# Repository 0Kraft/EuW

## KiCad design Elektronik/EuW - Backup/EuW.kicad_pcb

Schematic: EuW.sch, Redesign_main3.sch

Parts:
C1, C4: 220; E2_5RE
C2, C3: 104; C025-024X044
D1: 14001; DO41-7.6
J3, J4: 1X2-3.5MM
P1, P2: CONN_02X05; Pin_Header_Angled_2x05_Pitch2.54mm
P4: CONN_01X03; Pin_Header_Straight_1x03_Pitch2.54mm
Q1, Q3, Q5: BC548; TO-92_Molded_Narrow
Q2, Q4: IRF4905; TO-220_Vertical
R1, R2, R3, R4, R11, R12: 10000; 0207_2V
R5, R6, R7, R8: 10MOhm; 0207_2V
R9: 470; 0207_2V
R10: 970; 0207_2V
U$1: NANO
U$2: RPI-ZERO; RASPBERRYPI_BASTELSTUBE_V13_RASPI_BOARD_B+_FULL
U$3, U$4: CP8-ADJ

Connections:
/5V0@1: C1.+, D1.C, Q4.3, R4.2, U$1.5V (5.5V)
/5VRPI: Q4.2, R12.1, U$2.2 (5V0)
/D2: P1.1, U$1.D2
/D3: P1.3, U$1.D3
/D4: P1.5, U$1.D4
/D5: P1.7, U$1.D5
/D6: P1.9, U$1.D6
/D7: P2.1, U$1.D7
/D8: P2.3, U$1.D8
/D9: P2.5, U$1.D9
/D10: P2.7, U$1.D10
/D11: P2.9, U$1.D11
/N$1: D1.A, U$4.OUT+
/N$3: J4.2, Q2.3, R2.2, R6.1
/N$11: J3.2, R8.1, U$4.IN+
/N$12: J3.1, U$4.IN-
/N$14: C3.2, R7.1, R8.2, U$1.A1
/N$15: R9.1, U$1.TX0
/N$16: Q5.1, R12.2, U$1.RX1
/N$17: Q5.3, U$2.8 (TXD0/GPIO14)
/N$18: R9.2, R10.1, U$2.10 (RXD0/GPIO15)
/N$20: C4.+, U$1.RST
GND: C1.-, C2.2, C3.1, J4.1, P1.6, P1.8, P1.10, P2.6, P2.8, P2.10, P4.1, Q1.3, Q3.3, R5.1, R7.2, R10.2, U$1.GND1 (GND2), U$2.9 (GND), U$3.IN-, U$3.OUT-, U$4.OUT-; also elsewhere on the board
unnamed: C2.1, R5.2, R6.2, U$1.A2
unnamed: C4.-, U$1.GND
unnamed: P1.2, P1.4, P2.2, P2.4, P4.2, U$3.OUT+
unnamed: P4.3, U$1.A0
unnamed: Q1.1, Q2.1, R2.1
unnamed: Q1.2, R1.1
unnamed: Q2.2, U$3.IN+
unnamed: Q3.1, Q4.1, R4.1
unnamed: Q3.2, R3.1
unnamed: Q5.2, R11.1
unnamed: R1.2, U$1.A6
unnamed: R3.2, U$1.A7
unnamed: R11.2, U$2.1 (3V3)

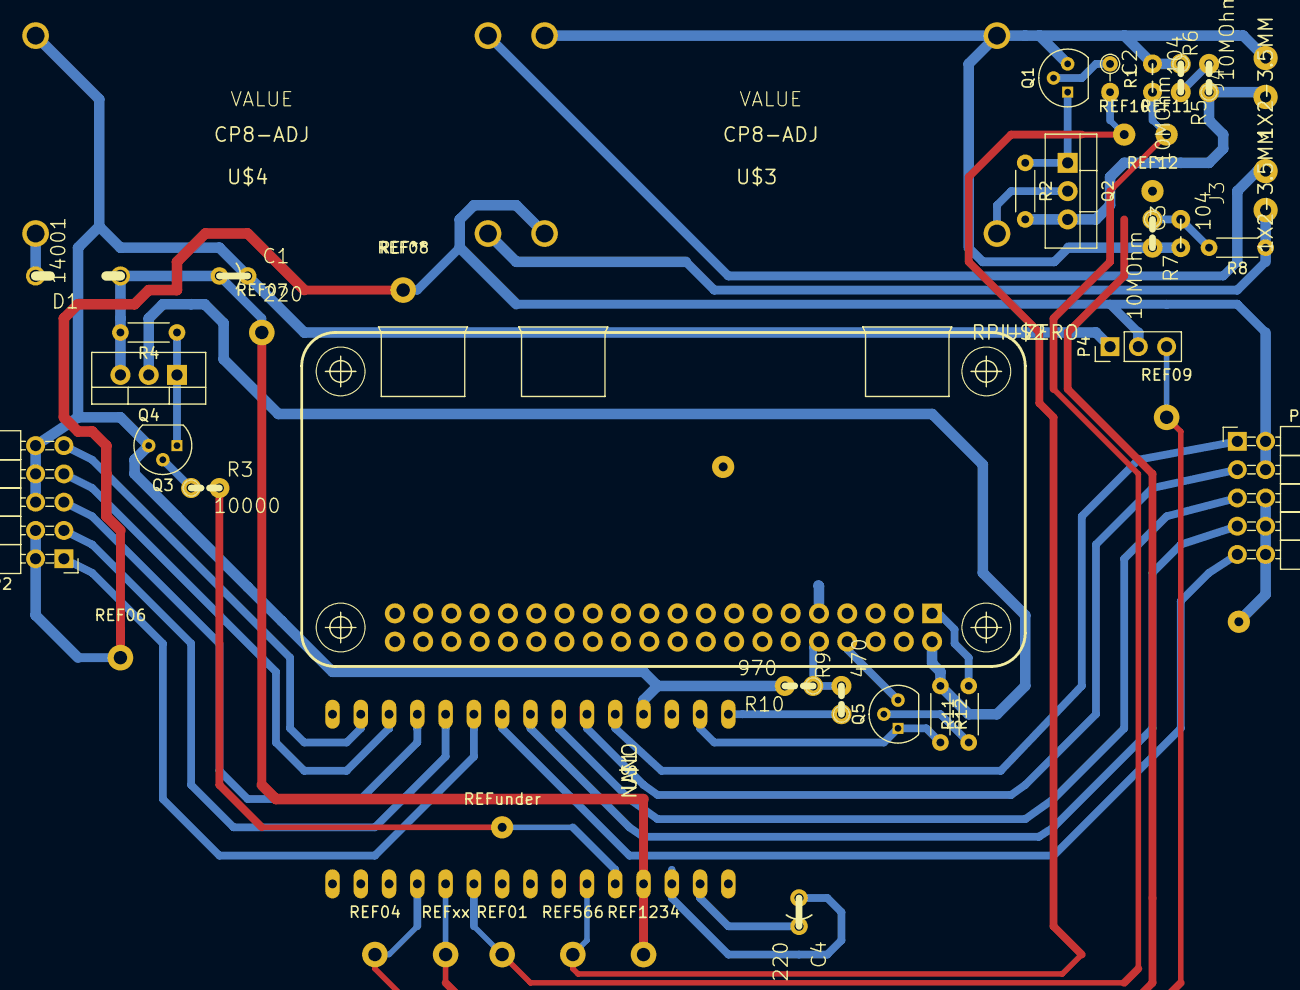
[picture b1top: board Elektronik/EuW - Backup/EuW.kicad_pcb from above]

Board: 2 copper layers, 45 parts (0 on the bottom side), 36 nets.

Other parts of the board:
REF01, REF04, REF06, REF07, REF08, REF09, REF566, REF1234: SolderWirePad_single_1-2mmDrill
REF10, REF11, REF12: SolderWirePad_single_0-8mmDrill
REFunder: SolderWirePad_single_0-8mmDrill
REFxx: SolderWirePad_single_1-2mmDrill
qwe: WireConnection_0-8mmDrill; WireConnection_0.80mmDrill

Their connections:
GND: qwe.1, qwe.2; also elsewhere on the board

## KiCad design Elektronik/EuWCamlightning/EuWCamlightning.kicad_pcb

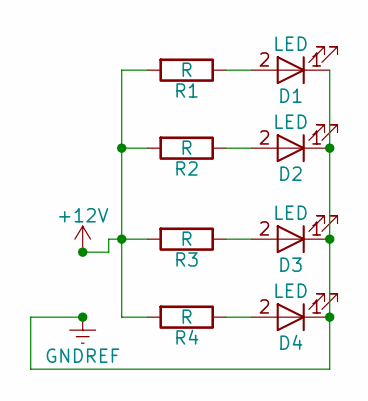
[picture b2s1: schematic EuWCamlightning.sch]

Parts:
D1, D2, D3, D4: LED; LED_0805_HandSoldering
R1, R2, R3, R4: R; R_0805_HandSoldering

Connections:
+12V: R1.2, R2.2, R3.2, R4.2
GNDREF: D1.1 (K), D2.1 (K), D3.1 (K), D4.1 (K)
unnamed: D1.2 (A), R1.1
unnamed: D2.2 (A), R2.1
unnamed: D3.2 (A), R3.1
unnamed: D4.2 (A), R4.1

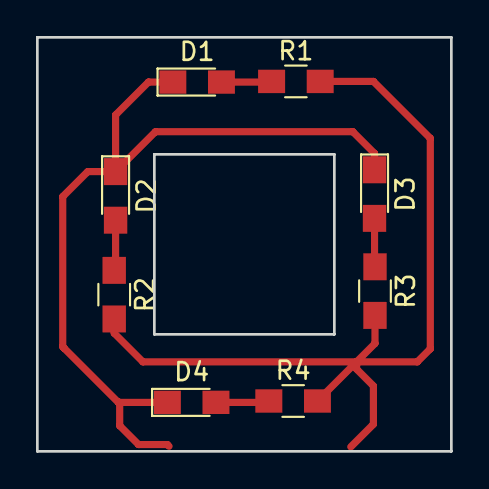
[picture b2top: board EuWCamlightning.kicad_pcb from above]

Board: 2 copper layers, 23.0 x 23.0 mm, 8 parts (0 on the bottom side), 6 nets.

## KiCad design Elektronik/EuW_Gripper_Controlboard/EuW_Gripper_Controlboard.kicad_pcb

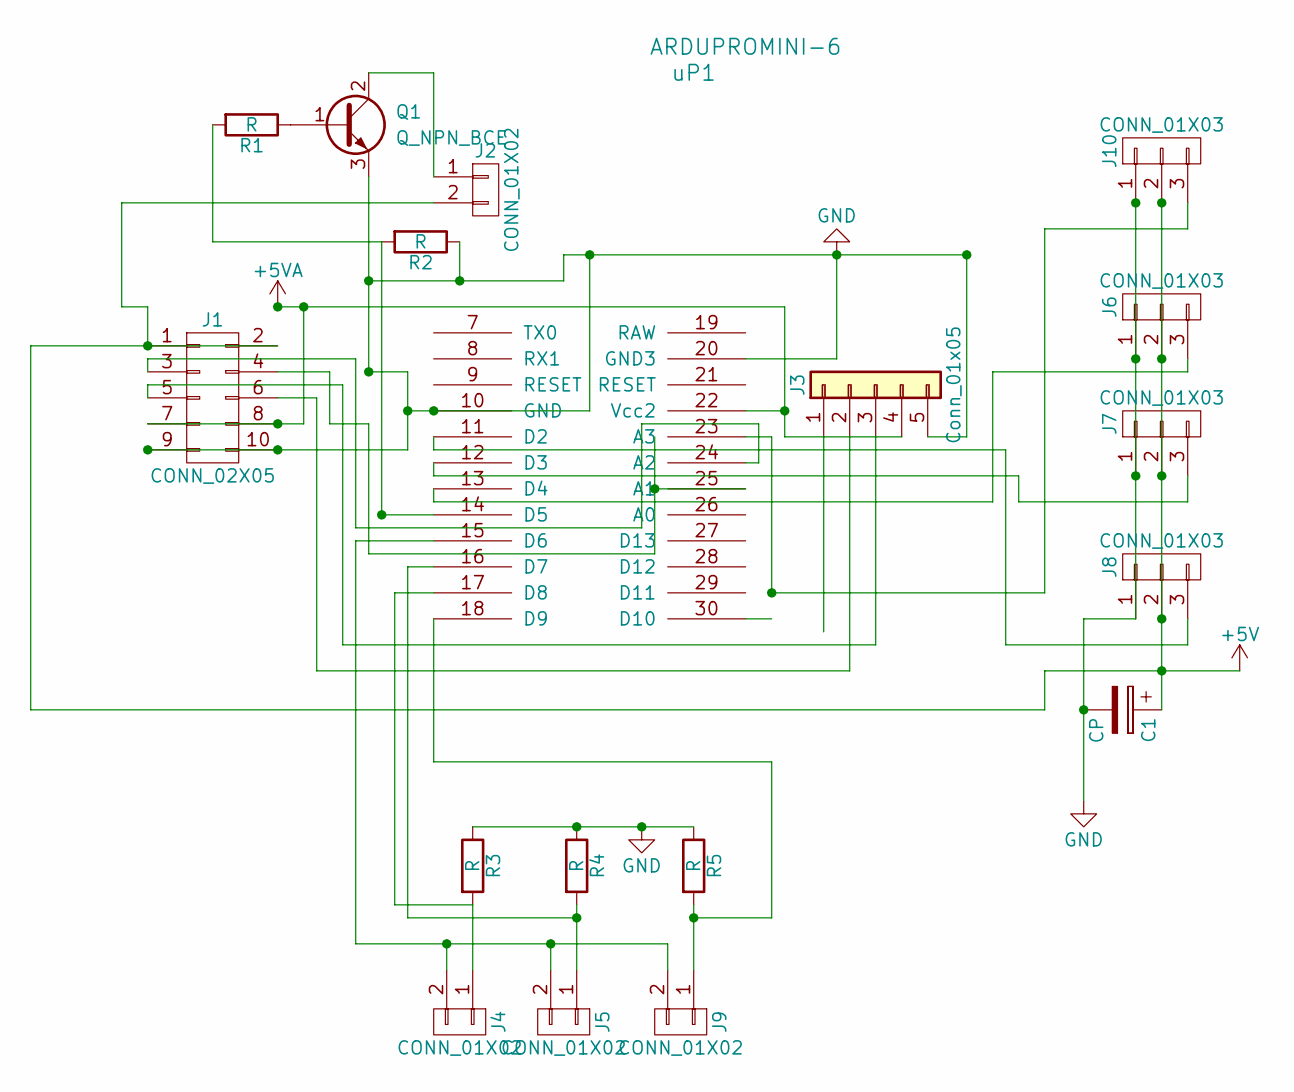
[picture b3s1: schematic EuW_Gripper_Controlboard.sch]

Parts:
C1: CP; CP_Radial_D6.3mm_P2.50mm
J1: CONN_02X05; Pin_Header_Angled_2x05_Pitch2.54mm
J2, J4, J5, J9: CONN_01X02; Pin_Header_Straight_1x02_Pitch2.54mm
J3: Conn_01x05; Pin_Header_Straight_1x05_Pitch2.54mm
J6, J7, J8, J10: CONN_01X03; Pin_Header_Straight_1x03_Pitch2.54mm
Q1: Q_NPN_BCE; SOT-89-3_Handsoldering
R1, R2, R3, R4, R5: R; R_1206_HandSoldering
uP1: ARDUPROMINI-6; ArduProMini-6

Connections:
+5V: C1.1, J1.1, J1.2, J2.2, J6.2, J7.2, J8.2, J10.2
+5VA: J1.7, J1.8, J3.4, uP1.22 (Vcc2)
GND: C1.2, J1.9, J1.10, J3.5, J6.1, J7.1, J8.1, J10.1, Q1.3 (E), R2.1, R3.1, R4.1, R5.1, uP1.10 (GND), uP1.20 (GND3)
unnamed: J1.3, uP1.24 (A2)
unnamed: J1.4, uP1.25 (A1)
unnamed: J1.5, J3.3, uP1.31
unnamed: J1.6, J3.2, uP1.32
unnamed: J2.1, Q1.2 (C)
unnamed: J4.1, R3.2, uP1.17 (D8)
unnamed: J4.2, J5.2, J9.2, uP1.15 (D6)
unnamed: J5.1, R4.2, uP1.16 (D7)
unnamed: J6.3, uP1.13 (D4)
unnamed: J7.3, uP1.12 (D3)
unnamed: J8.3, uP1.11 (D2)
unnamed: J9.1, R5.2, uP1.18 (D9)
unnamed: J10.3, uP1.23 (A3)
unnamed: Q1.1 (B), R1.1
unnamed: R1.2, R2.2, uP1.14 (D5)

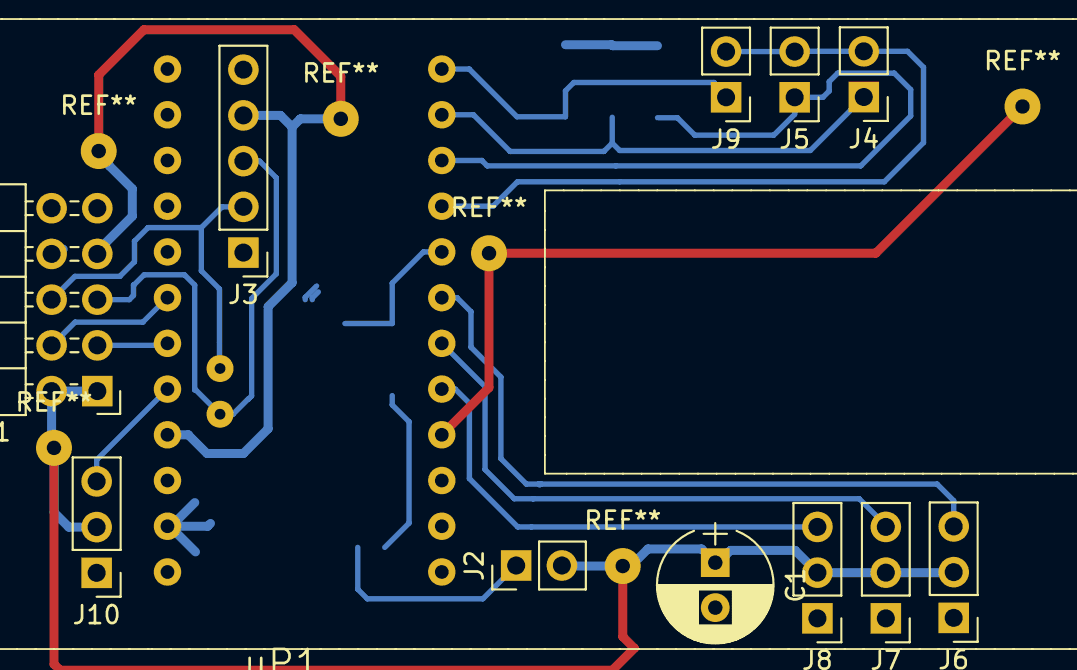
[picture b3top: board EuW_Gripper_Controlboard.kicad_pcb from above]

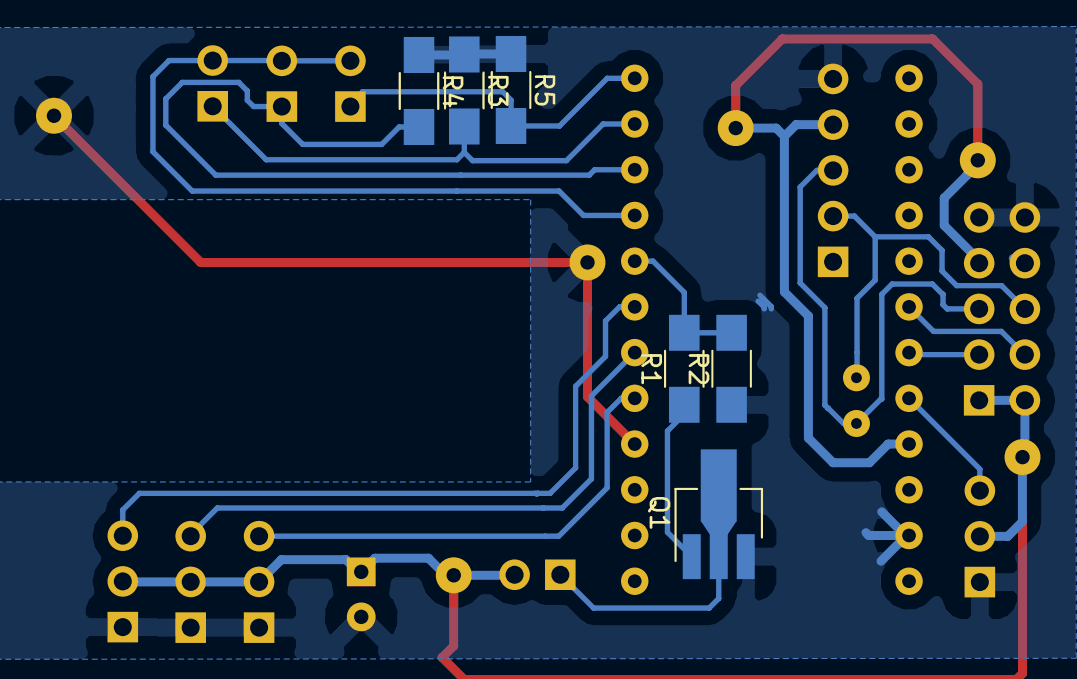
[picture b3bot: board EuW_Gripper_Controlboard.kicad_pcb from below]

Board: 2 copper layers, 18 parts (6 on the bottom side), 18 nets.

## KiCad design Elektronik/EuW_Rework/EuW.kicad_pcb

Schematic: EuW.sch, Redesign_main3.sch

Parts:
C1, C4: 220; CP_Radial_D5.0mm_P2.50mm
C2, C3: 104; C_0805_HandSoldering
D1: 14001; D_SMA
J3, J4: 1X2-3.5MM
P1, P2: CONN_02X05; Pin_Header_Angled_2x05_Pitch2.54mm
P4: CONN_01X03; Pin_Header_Straight_1x03_Pitch2.54mm
Q1, Q2, Q3: BC848; SOT-23_Handsoldering
Q4, Q5: IRF4905; TO-220-3_Horizontal
R1, R2, R3, R4, R12: 10000; R_1206_HandSoldering
R5, R6, R7, R8: 10MOhm; R_1206_HandSoldering
R9: 470; R_1206_HandSoldering
R10: 970; R_1206_HandSoldering
R11: 10000; R_Axial_DIN0204_L3.6mm_D1.6mm_P5.08mm_Horizontal
R13, R14: 4700; R_1206_HandSoldering
U$1: NANO
U$2: RPI-ZERO; RASPBERRYPI_BASTELSTUBE_V13_RASPI_BOARD_B+_FULL
U$3, U$4: CP8-ADJ; XL6009

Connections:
/5V0@1: C1.+, D1.C, P1.7, P1.8, P2.7, P2.8, Q5.3 (S), R4.2, R13.1, R14.1, U$1.5V (5.5V)
/5VRPI: Q5.2 (D), R12.1, U$2.2 (5V0)
/N$1: D1.A, U$4.OUT+
/N$3: J4.2, Q4.3 (S), R2.2, R6.1
/N$7: P1.3, U$1.D3
/N$9: P1.4, U$1.D2
/N$10: J4.1, U$3.IN-
/N$11: J3.2, R8.1, U$4.IN+
/N$12: J3.1, U$4.IN-
/N$14: C3.2, R7.1, R8.2, U$1.A1; also elsewhere on the board
/N$15: R9.1, U$1.TX0
/N$16: Q3.3 (C), R12.2, U$1.RX1
/N$17: Q3.2 (E), U$2.8 (TXD0/GPIO14)
/N$18: R9.2, R10.1, U$2.10 (RXD0/GPIO15)
/N$20: C4.+, U$1.RST
GND: C1.-, C2.2, C3.1, P1.9, P1.10, P2.9, P2.10, P4.1, Q1.2 (E), Q2.2 (E), R5.1, R7.2, R10.2, U$1.GND1 (GND2), U$2.9 (GND), U$3.OUT-, U$4.OUT-
unnamed 16: C2.1, R5.2, R6.2, U$1.A2; also elsewhere on the board
unnamed: C4.-, U$1.GND
unnamed: P1.1, P1.2, P2.1, P2.2, P4.2, U$3.OUT+
unnamed: P1.5, P2.5, R13.2, U$1.A5
unnamed: P1.6, P2.6, R14.2, U$1.A4
unnamed: P2.3, U$1.D11
unnamed: P2.4, U$1.D12
unnamed: P4.3, U$1.D9
unnamed: Q1.1 (B), R1.1
unnamed: Q1.3 (C), Q4.1 (G), R2.1
unnamed: Q2.1 (B), R3.1
unnamed: Q2.3 (C), Q5.1 (G), R4.1
unnamed: Q3.1 (B), R11.1
unnamed: Q4.2 (D), U$3.IN+
unnamed: R1.2, U$1.A3
unnamed: R3.2, U$1.D10
unnamed: R11.2, U$2.1 (3V3)

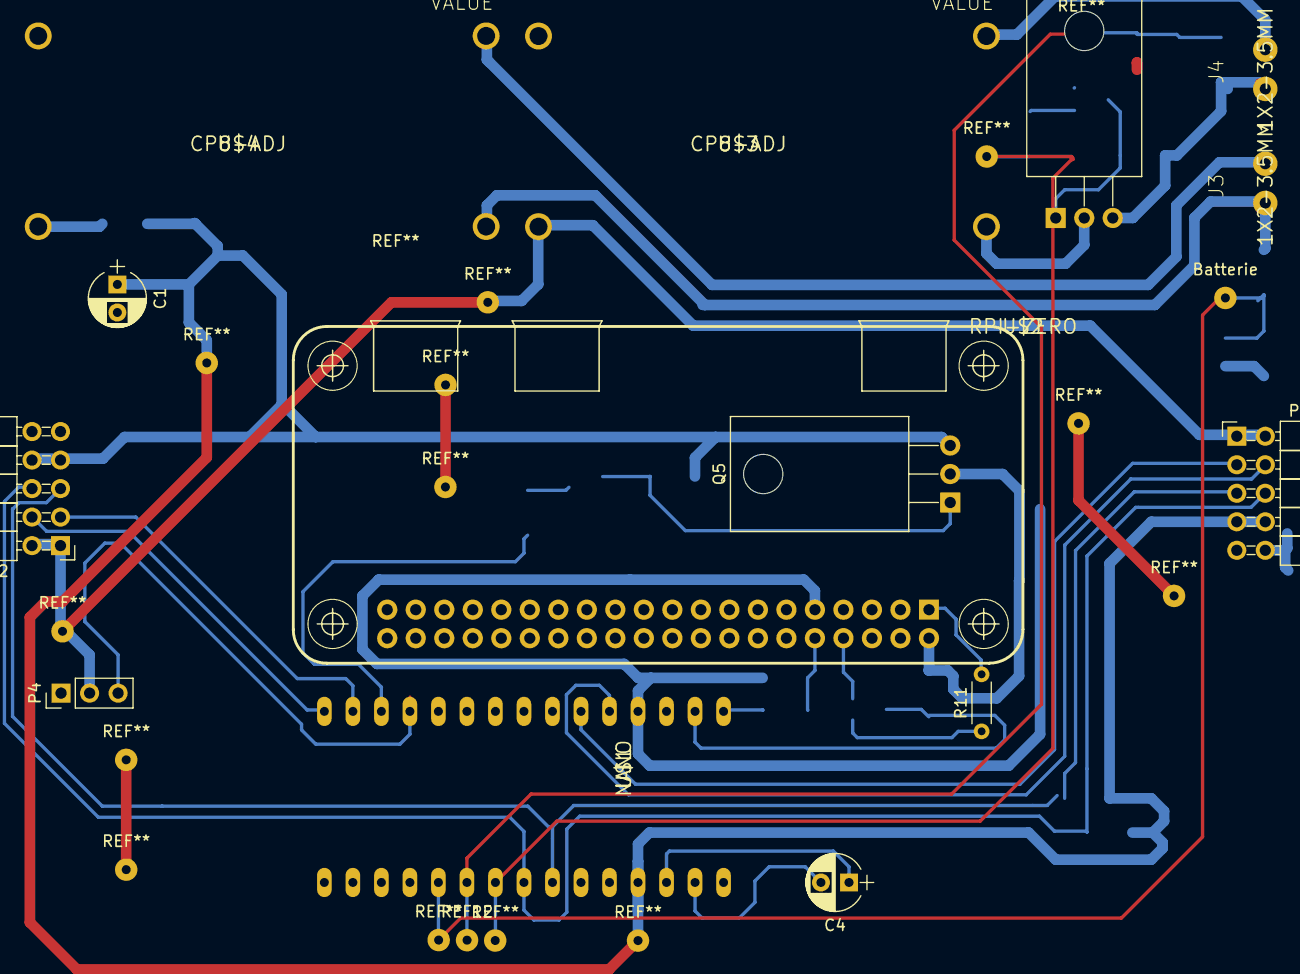
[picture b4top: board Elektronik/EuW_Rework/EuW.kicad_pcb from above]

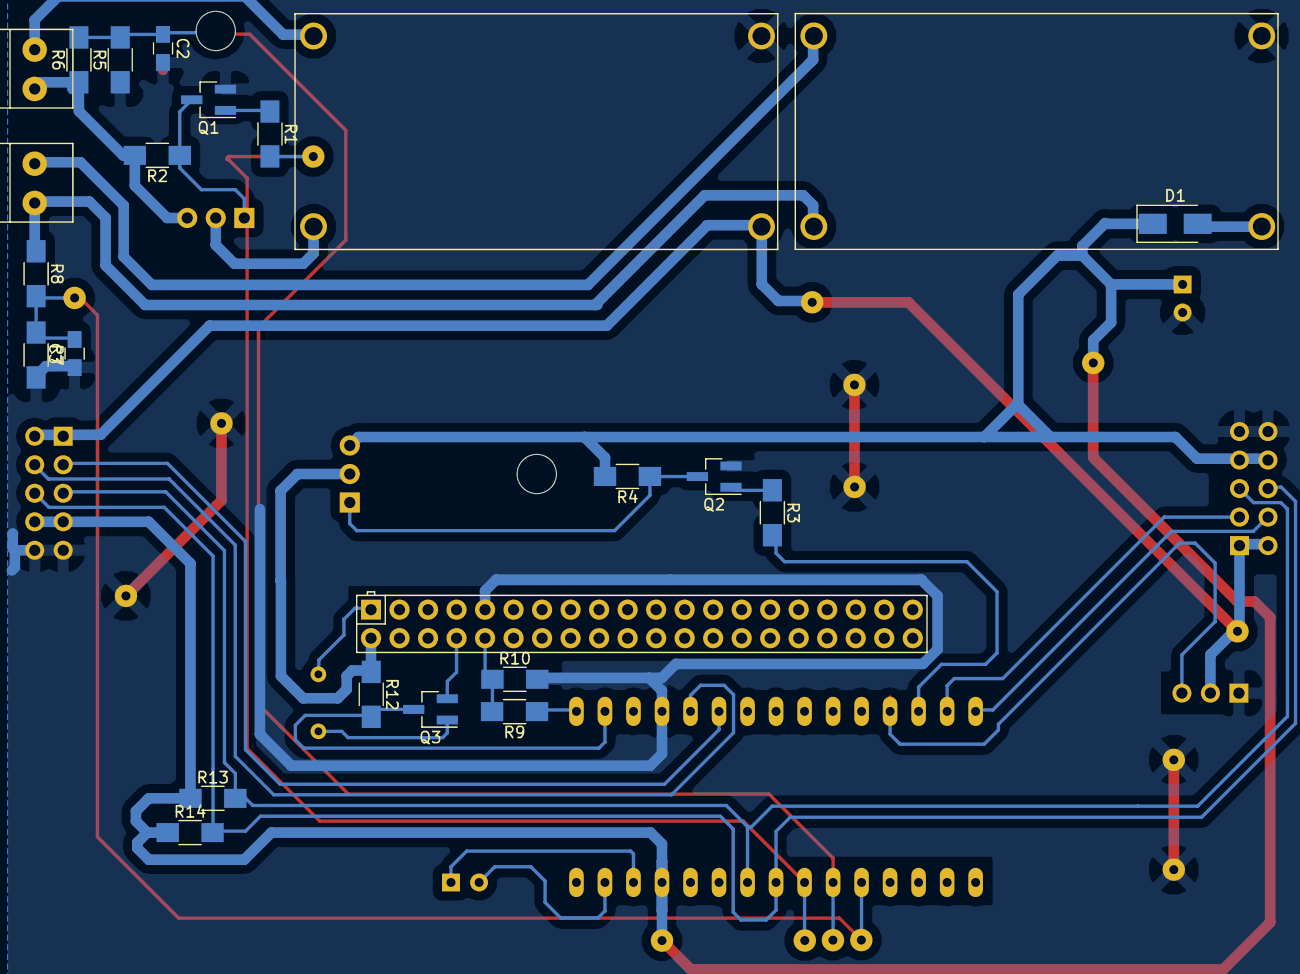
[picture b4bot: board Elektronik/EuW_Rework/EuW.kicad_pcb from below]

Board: 2 copper layers, 35 parts (19 on the bottom side), 33 nets.

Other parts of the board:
Batterie: SolderWirePad_single_0-8mmDrill
REF12: SolderWirePad_single_0-8mmDrill

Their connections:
/N$14: Batterie.1; also elsewhere on the board
unnamed 16: REF12.1; also elsewhere on the board

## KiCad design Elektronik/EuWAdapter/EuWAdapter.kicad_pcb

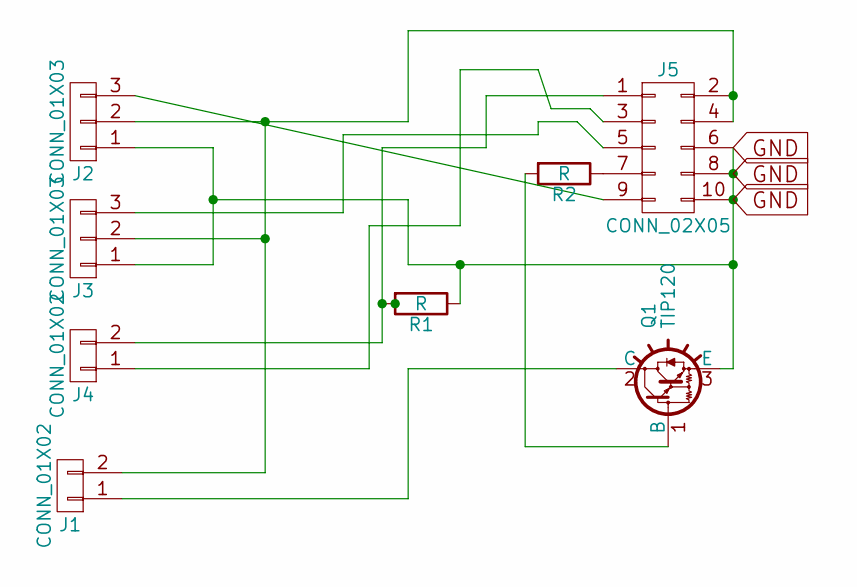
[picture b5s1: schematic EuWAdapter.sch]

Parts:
J1, J4: CONN_01X02; Pin_Header_Straight_1x02_Pitch2.54mm
J2, J3: CONN_01X03; Pin_Header_Straight_1x03_Pitch2.54mm
J5: CONN_02X05; Pin_Header_Angled_2x05_Pitch2.54mm
Q1: TIP120; TO-220_Vertical
R1, R2: R; R_Axial_DIN0204_L3.6mm_D1.6mm_P7.62mm_Horizontal

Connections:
GND: J2.1, J3.1, J5.6, J5.8, J5.10, Q1.3 (E), R1.1
unnamed: J1.1, Q1.2 (C)
unnamed: J1.2, J2.2, J3.2, J5.2, J5.4
unnamed: J2.3, J5.9
unnamed: J3.3, J5.5
unnamed: J4.1, J5.3
unnamed: J4.2, J5.1, R1.2
unnamed: J5.7, R2.1
unnamed: Q1.1 (B), R2.2

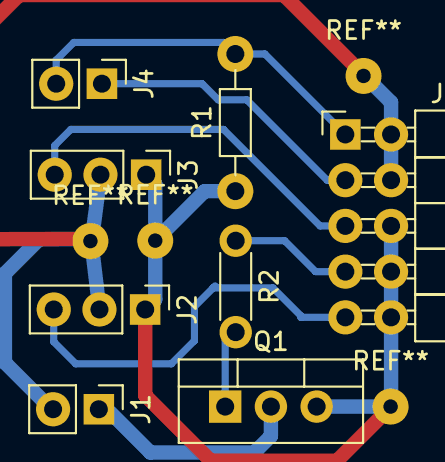
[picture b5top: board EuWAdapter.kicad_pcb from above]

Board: 2 copper layers, 8 parts (0 on the bottom side), 9 nets.

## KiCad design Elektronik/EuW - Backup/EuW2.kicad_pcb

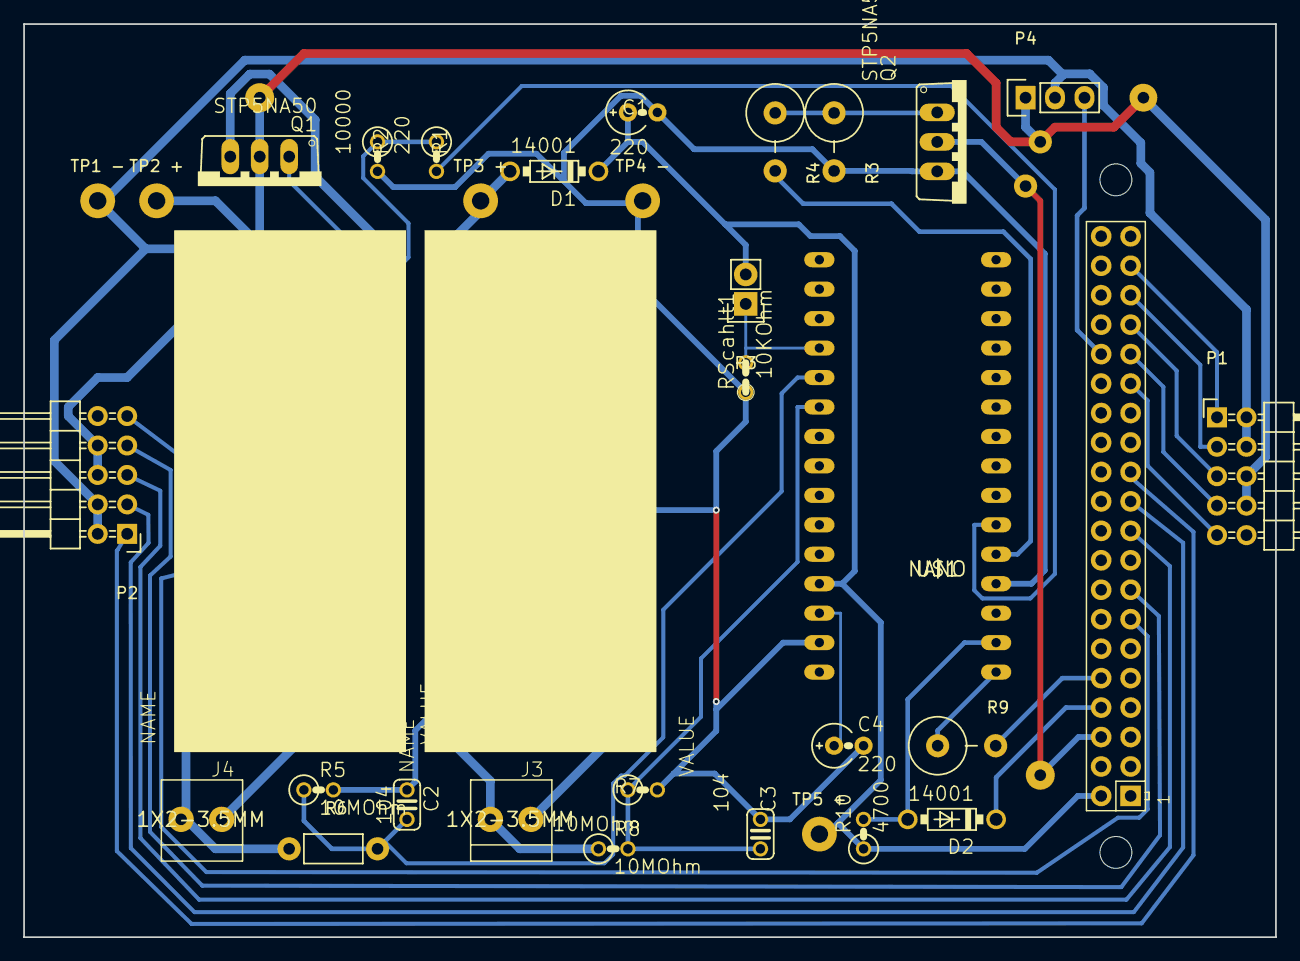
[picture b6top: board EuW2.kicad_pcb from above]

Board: 2 copper layers, 108.0 x 78.7 mm, 39 parts (0 on the bottom side), 34 nets.

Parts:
C1, C4: 220; E2,5RE
C2, C3: 104; C025-024X044
D1, D2: 14001; DO41-7.6
J3, J4: 1X2-3.5MM
P1, P2: CONN_02X05; Pin_Header_Angled_2x05
P3: CONN_01X02; Pin_Header_Straight_1x02
P4: CONN_01X03; Socket_Strip_Straight_1x03
Q1, Q2: STP5NA50; TO220BV
R1: 220; 0207%2f2V
R2: 10000; 0207%2f2V
R3: 10000; Resistor_Vertical_RM5mm
R4: 220; Resistor_Vertical_RM5mm
R5, R7, R8: 10MOhm; 0207%2f2V
R6: 10MOhm; Resistor_Horizontal_RM7mm
R9: 4700; Resistor_Vertical_RM5mm
R10: 4700; 0207%2f2V
RScahlt1: 10KOhm; 0207_2V
TP1 -, TP2 +, TP3 +, TP4 -, TP5 +: Measurement_Point_Round-TH_Big
U$1: NANO
U$2: RPI-ZERO; RASPBERRYPI_BASTELSTUBE_V13_RASPI_BOARD_B+_FULL
U$3, U$4: CP8-ADJ
pad2, pad6, pad7, pad8, pad10: pad

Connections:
/5V0@1: C1.+, D1.C, P3.2, R10.1, TP5 +.1, U$1.5V, U$2.2
/GND_M~: Q2.D, U$2.6, pad6.1, pad7.1
/N$1: D1.A, TP3 +.1, U$4.OUT+
/N$2: Q2.G, R3.1, R4.1
/N$3: P1.2, P1.4, P2.2, P2.4, P4.2, TP1 -.1, U$3.OUT+
/N$4: C2.2, R5.1, R6.2, U$1.A1
/N$5: P1.6, P1.8, P2.6, P2.8, P4.1, Q1.D, TP2 +.1, pad2.1, pad8.1, pad10.1
/N$6: J4.2, R6.1, U$3.IN+
/N$7: R1.2, U$1.D3
/N$8: Q1.G, R1.1, R2.1
/N$9: R4.2, U$1.D2
/N$10: J4.1, U$3.IN-
/N$11: J3.2, R8.1, U$4.IN+
/N$12: J3.1, U$4.IN-
/N$13: Q1.S, U$3.OUT-
/N$14: C3.2, R7.1, R8.2, U$1.A2
/N$15: R9.1, U$1.TX0
/N$16: D2.A, R10.2, U$1.RX1
/N$17: D2.C, U$2.8
/N$18: R9.2, U$2.10
/N$20: C4.+, U$1.RST
GND: C1.-, C2.1, C3.1, C4.-, Q2.S, R2.2, R3.2, R5.2, R7.2, RScahlt1.1, TP4 -.1, U$1.GND, U$1.GND1, U$4.OUT-
unnamed: P1.1, U$2.37
unnamed: P1.3, U$2.35
unnamed: P1.5, U$2.33
unnamed: P1.7, U$2.31
unnamed: P1.9, U$2.29
unnamed: P2.1, U$2.23
unnamed: P2.3, U$2.21
unnamed: P2.5, U$2.19
unnamed: P2.7, U$2.15
unnamed: P2.9, U$2.13
unnamed: P3.1, RScahlt1.2, U$1.A0
unnamed: P4.3, U$2.32

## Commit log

2017-09-26 setup
2018-07-24 update EUW_I2C
2018-08-14 OKraft
2018-08-28 I2C communication update
